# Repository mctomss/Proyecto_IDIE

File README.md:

# Proyecto_IDIE - Medidor de Variables Eléctricas con Control Remoto
by: 
- Juan Andres Rodriguez Ruiz
- Juan Andres Abella Ballen
- Tomás Felipe Montañez Piñeros

Este repositorio contiene el diseño y firmware de un **circuito medidor de variables eléctricas**, capaz de monitorear y controlar una carga conectada a la red doméstica. El dispositivo se comunica a través de **MQTT**, permitiendo visualizar las mediciones y controlar la carga desde un celular o computador.

## Descripción

El sistema está compuesto por:

1. **Firmware:** Código en Arduino para la adquisición y transmisión de datos mediante MQTT.
2. **Diseño Electrónico:** Archivos del circuito diseñados en **Eagle**.
3. **Footprints, Librerías y Datasheets:** Recursos adicionales para la correcta implementación del circuito.
4. **Archivos Gerber:** Listos para la fabricación de la PCB.

## Tecnologías Utilizadas

- **Código:** Arduino (C++)
- **Protocolo de comunicación:** MQTT
- **Diseño de PCB:** Eagle
- **Archivos de fabricación:** Gerber, .brd, .sch, .epf, .cam 

## Advertencia Importante

Para la compilación del firmware, **es obligatorio utilizar las librerías proporcionadas en este repositorio**.  
Se han realizado modificaciones en ciertas partes de las librerías para garantizar el correcto funcionamiento del sistema, especialmente en una sección de atención.  
El uso de versiones estándar de estas librerías puede causar fallos en la compilación.

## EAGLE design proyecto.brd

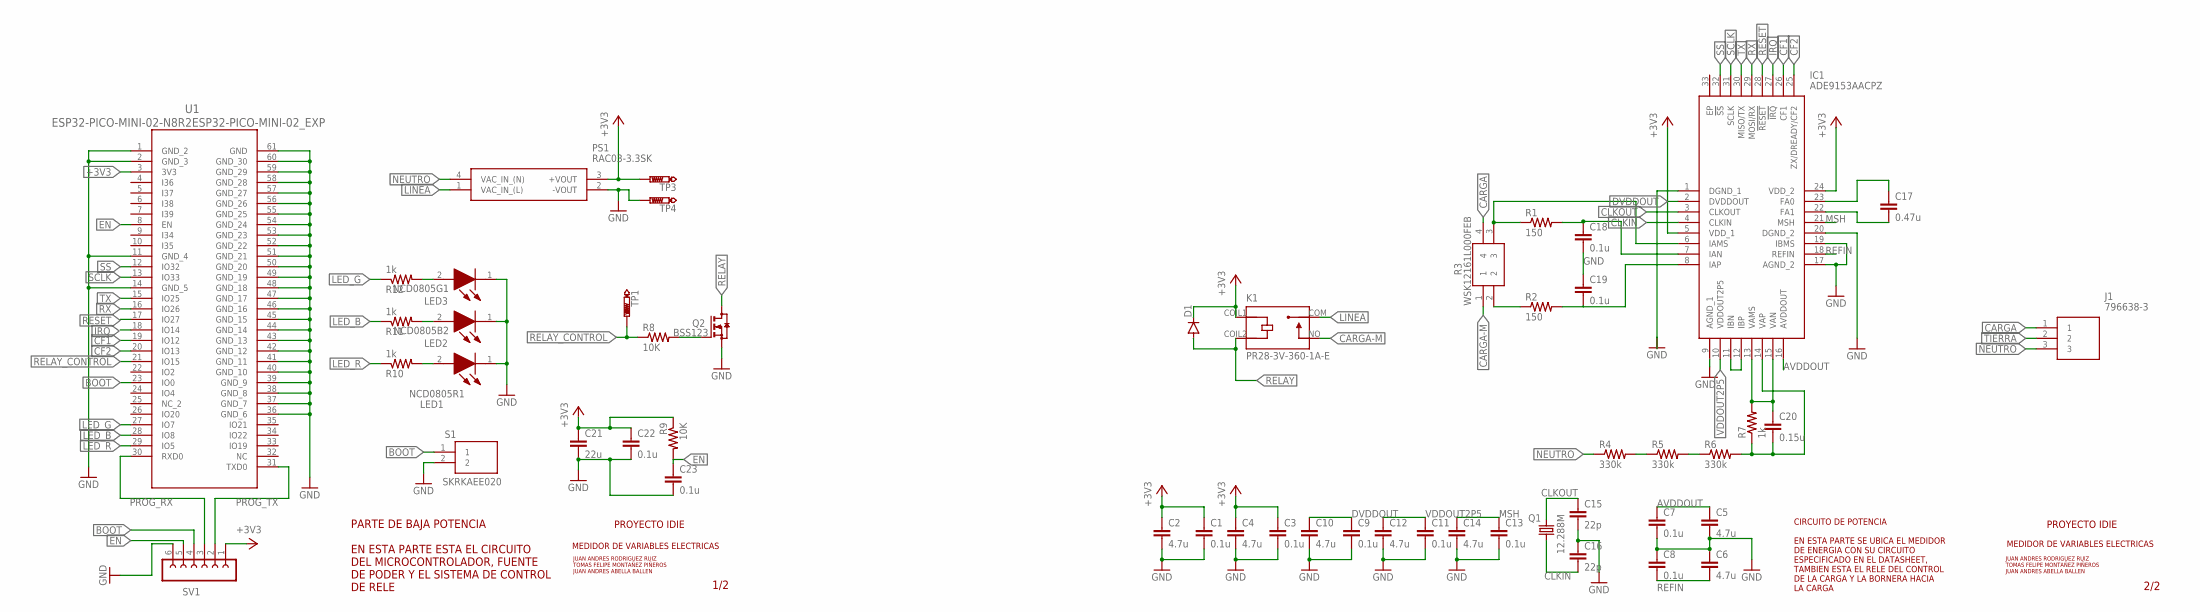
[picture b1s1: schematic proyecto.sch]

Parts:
C1, C3, C7, C8, C9, C11, C13, C18, C19, C22, C23: 0.1u; C0402K
C2, C4, C5, C6, C10, C12, C14: 4.7u; C0402K
C15, C16: 22p; C0402K
C17: 0.47u; C0402K
C20: 0.15u; C0402K
C21: 22u; C0402K
D1: DIODE-SMB; SMB
IC1: ADE9153AACPZ; QFN50P500X500X80-33N
J1: 796638-3; SHDRRA3W102P0X508_1X3_1706X120
K1: PR28-3V-360-1A-E; RELAY_PR28-3V-360-1A-E
LED1: NCD0805R1; LEDC2012X120N
LED2: NCD0805B2; LEDC2012X120N
LED3: NCD0805G1; LEDC2012X120N
PS1: RAC03-3.3SK; RAC0305SK
Q1: 12.288M; 2.0X1.6_KX-5
Q2: BSS123; SOT23
R1, R2: 150; R0402
R3: WSK12161L000FEB
R4, R5, R6: 330k; R0603
R7: 1k; R0603
R8, R9: 10K; R0402
R10, R11, R12: 1k; R0402
S1: SKRKAEE020
SV1: FE06-1; FE06
TP1, TP3, TP4: PTR1TP10R; TP10R
U1: ESP32-PICO-MINI-02-N8R2ESP32-PICO-MINI-02_EXP; ESP32-PICO-MINI-02_EXP

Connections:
+3V3: C1.1, C2.1, C3.1, C4.1, C21.1, C22.1, D1.C, IC1.5 (VDD_1), IC1.24 (VDD_2), K1.COIL1, PS1.3 (+VOUT), R9.1, SV1.1, TP3.TP, U1.3 (3V3)
AVDDOUT: C5.1, C7.1, IC1.16 (AVDDOUT)
BOOT: S1.1, SV1.4, U1.23 (IO0)
CARGA-M: K1.NO, R3.1
CF1: IC1.26 (CF1), U1.19 (IO12)
CF2: IC1.25 (ZX/DREADY/CF2), U1.20 (IO13)
CLKIN: C16.2, IC1.4 (CLKIN), Q1.1
CLKOUT: C15.1, IC1.3 (CLKOUT), Q1.3 (2)
DVDDOUT: C9.1, C10.1, IC1.2 (DVDDOUT)
EN: C23.1, R9.2, SV1.5, U1.8 (EN)
GND: C1.2, C2.2, C3.2, C4.2, C5.2, C6.1, C7.2, C8.1, C9.2, C10.2, C11.2, C12.2, C13.2, C14.2, C15.2, C16.1, C18.2, C19.1, C21.2, C22.2, C23.2, IC1.1 (DGND_1), IC1.9 (AGND_1), IC1.17 (AGND_2), IC1.19 (IBMS), IC1.20 (DGND_2), LED1.1 (K), LED2.1 (K), LED3.1 (K), PS1.2 (-VOUT), Q2.2 (S), S1.2, SV1.6, TP4.TP, U1.1 (GND_2), U1.2 (GND_3), U1.11 (GND_4), U1.14 (GND_5), U1.36 (GND_6), U1.37 (GND_7), U1.38 (GND_8), U1.39 (GND_9), U1.40 (GND_10), U1.41 (GND_11), U1.42 (GND_12), U1.43 (GND_13), U1.44 (GND_14), U1.45 (GND_15), U1.46 (GND_16), U1.47 (GND_17), U1.48 (GND_18), U1.49 (GND_19), U1.50 (GND_20), U1.51 (GND_21), U1.52 (GND_22), U1.53 (GND_23), U1.54 (GND_24), U1.55 (GND_25), U1.56 (GND_26), U1.57 (GND_27), U1.58 (GND_28), U1.59 (GND_29), U1.60 (GND_30), U1.61 (GND)
IRQ: IC1.27 (!IRQ), U1.18 (IO14)
LED_B: R11.1, U1.28 (IO8)
LED_G: R12.1, U1.27 (IO7)
LED_R: R10.1, U1.29 (IO5)
LINEA: K1.COM, PS1.1 (VAC_IN_(L))
M: J1.1, R3.4
MSH: C13.1, C14.1, IC1.21 (MSH)
unnamed: C17.1, IC1.23 (FA0)
unnamed: IC1.6 (IAMS), R1.1, R3.3
unnamed: C18.1, IC1.7 (IAN), R1.2
unnamed: C17.2, IC1.22 (FA1)
unnamed: C19.2, IC1.8 (IAP), R2.2
unnamed: R2.1, R3.2
unnamed: R4.2, R5.1
unnamed: R5.2, R6.1
unnamed: C20.2, IC1.14 (VAP), R6.2, R7.1
unnamed: C20.1, IC1.13 (VAMS), IC1.15 (VAN), R7.2
unnamed: LED1.2 (A), R10.2
unnamed: LED2.2 (A), R11.2
unnamed: Q2.1 (G), R8.2
unnamed: LED3.2 (A), R12.2
unnamed: IC1.11 (IBN), IC1.12 (IBP)
NEUTRO: J1.3, PS1.4 (VAC_IN_(N)), R4.1
PROG_RX: SV1.3, U1.30 (RXD0)
PROG_TX: SV1.2, U1.31 (TXD0)
REFIN: C6.2, C8.2, IC1.18 (REFIN)
RELAY: D1.A, K1.COIL2, Q2.3 (D)
RELAY_CONTROL: R8.1, TP1.TP, U1.21 (IO15)
RESET: IC1.28 (!RESET), U1.17 (IO27)
RX: IC1.29 (MOSI/RX), U1.16 (IO26)
SCLK: IC1.31 (SCLK), U1.13 (IO33)
SS: IC1.32 (!SS), U1.12 (IO32)
TIERRA: J1.2
TX: IC1.30 (MISO/TX), U1.15 (IO25)
VDDOUT2P5: C11.1, C12.1, IC1.10 (VDDOUT2P5)

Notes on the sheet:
PROYECTO IDIE
MEDIDOR DE VARIABLES ELECTRICAS
JUAN ANDRES RODRIGUEZ RUIZ
TOMAS FELIPE MONTAÑEZ PIÑEROS
JUAN ANDRES ABELLA BALLEN
1/2
PARTE DE BAJA POTENCIA EN ESTA PARTE ESTA EL CIRCUITO DEL MICROCONTROLADOR, FUENTE DE PODER Y EL SISTEMA DE CONTROL DE RELE
2/2
CIRCUITO DE POTENCIA EN ESTA PARTE SE UBICA EL MEDIDOR DE ENERGIA CON SU CIRCUITO ESPECIFICADO EN EL DATASHEET, TAMBIEN ESTA EL RELE DEL CONTROL DE LA CARGA Y LA BORNERA HACIA LA CARGA

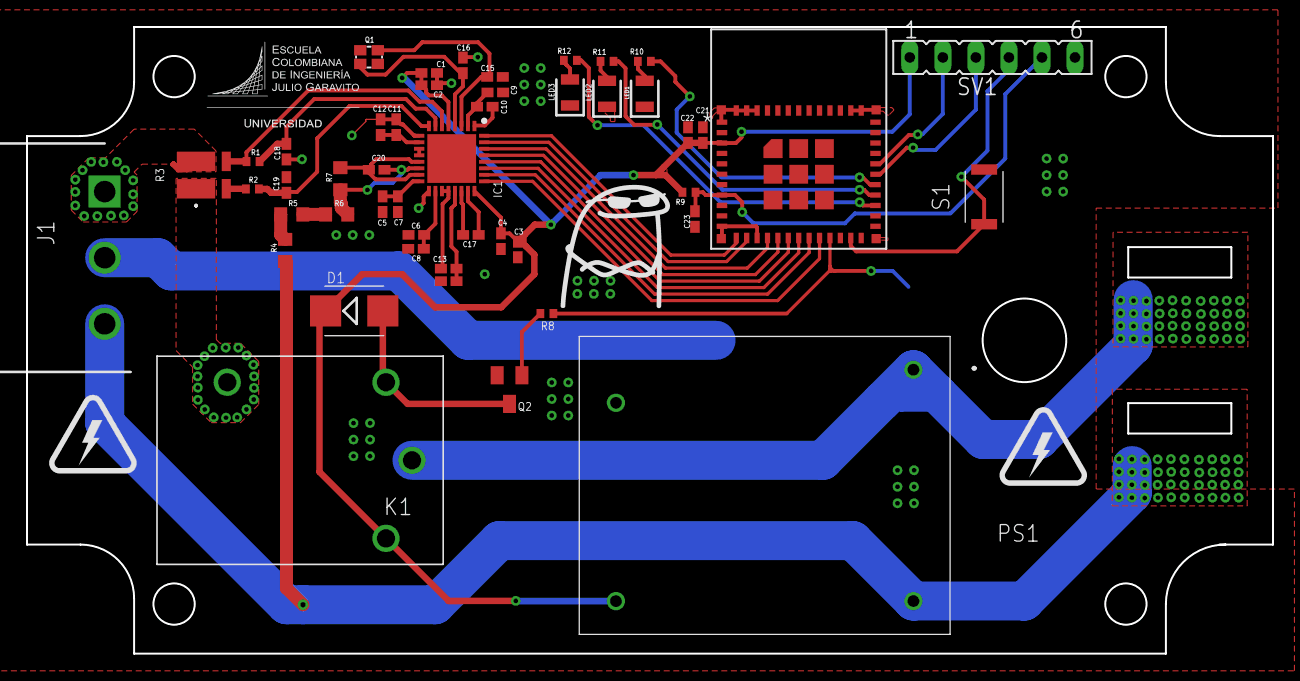
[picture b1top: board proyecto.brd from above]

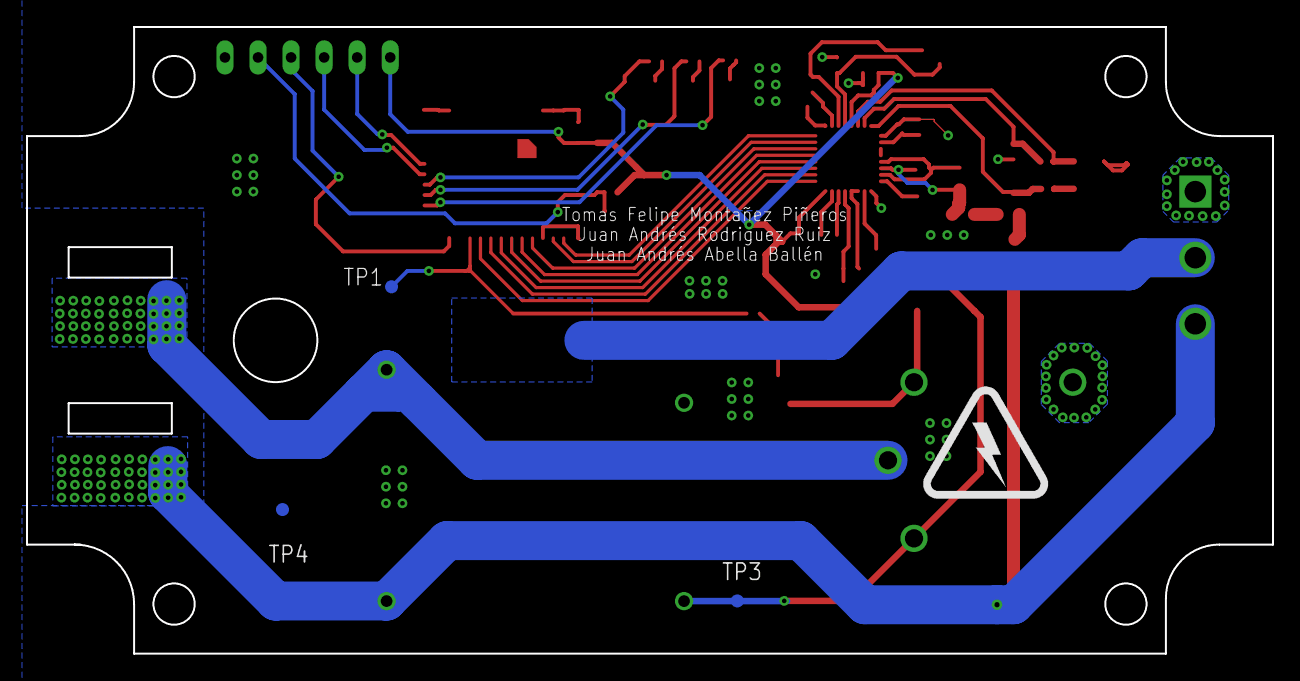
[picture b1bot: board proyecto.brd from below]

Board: 2 copper layers, 95.8 x 48.2 mm, 51 parts (3 on the bottom side), 45 nets.

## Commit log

2024-09-03 Creacion de proyecto en Eagle
    La plantilla de PCB esta termindada
2024-09-07 Avance :)
    .
2024-09-14 Condensadores de acople del integrado de medicion de energia
    Se añadio algunos condensadores de acople que se especifico en la hoja de datos del medidor de energia y el oscilador que se especifica.
2024-09-14 .
    .
2024-09-24 Conexiones según fabricante
    Se realizaron algunas conexiones de los condensadores de acople recomendados por el fabricante, se conecto tambien la resistencia Shunt y su filtro de antialising. Ademas se añadieron las resistencia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
    Por ultimo se añadio los condensadores de acople del ESP32
2024-09-24 Actualizacion del gitignore
    Se coloco un gitignore para no subir los autoguardados
2024-09-28 Transistor de rele y headers para programar
    Se añadio el transistor mosfet que va a controlar el rele, ademas del header para la programacion de microcontrolador
2024-10-05 Creacion de pistas y nuevos componentes
    Se hicieron las lineas criticas del circuito como lo son la fuente de alimentacion, linea, neutro, linea de medicion de corriente de la carga. Ademas se hicieron poligonos con el fin de conectar una 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
    Ademas se añadio el circuito del Enable del microcontrolador
2024-10-19 Se me daño :(
    .
2024-10-19 MINI avance
    No se avanzó tanto debido a que se me daño las pistas en plena clase :(
2024-10-25 Se añado y arreglo pistas
    Se arreglo las pistas de la fase y el neutro en las clavijas. Se añadieron otras pistas y se quito el boton del enable.
2024-10-26 Terminada la mayoria de conexiones
    Se realizo la gran mayoria de las conexiones, falta realizar las conexiones especificadas en el DRC.
2024-10-26 Errores DRC solucionados
    Se revisaron los errores DRC acerca de las conexiones faltantes. Ya no hay errores DRC. Falta montar diodos led indicativos y cambiar el boton de boot de ser necesario
2024-10-27 Diseño terminado
    Se termino el diseño del esquematico y de la PCB
2024-11-01 Se añadieron test pads
2024-11-02 Finalizado
2024-11-08 Adicion de pistas faltantes
2024-11-09 Code FIles
2024-11-10 Supongo que ya es el final
    :)
2024-11-10 todo listo
    :)
2024-11-11 WiFi connection done
2024-11-11 Fullt working HTTP Form
2024-11-11 MQTT Error while connecting!
2024-11-17 MQTT done
2024-11-23 XDIN
    XDIN
2024-12-14 Codigo terminado
    .
2024-12-17 Final Version
2024-12-17 Erase Trash
2025-03-10 Update README.md
    README.md Editado

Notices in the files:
parts and their libraries:
crystal-geyer_V1_0: Copyright: Geyer-Electronic
COPYRIGHT: Copyright (C) 2024 Ultra Librarian. All rights reserved.
